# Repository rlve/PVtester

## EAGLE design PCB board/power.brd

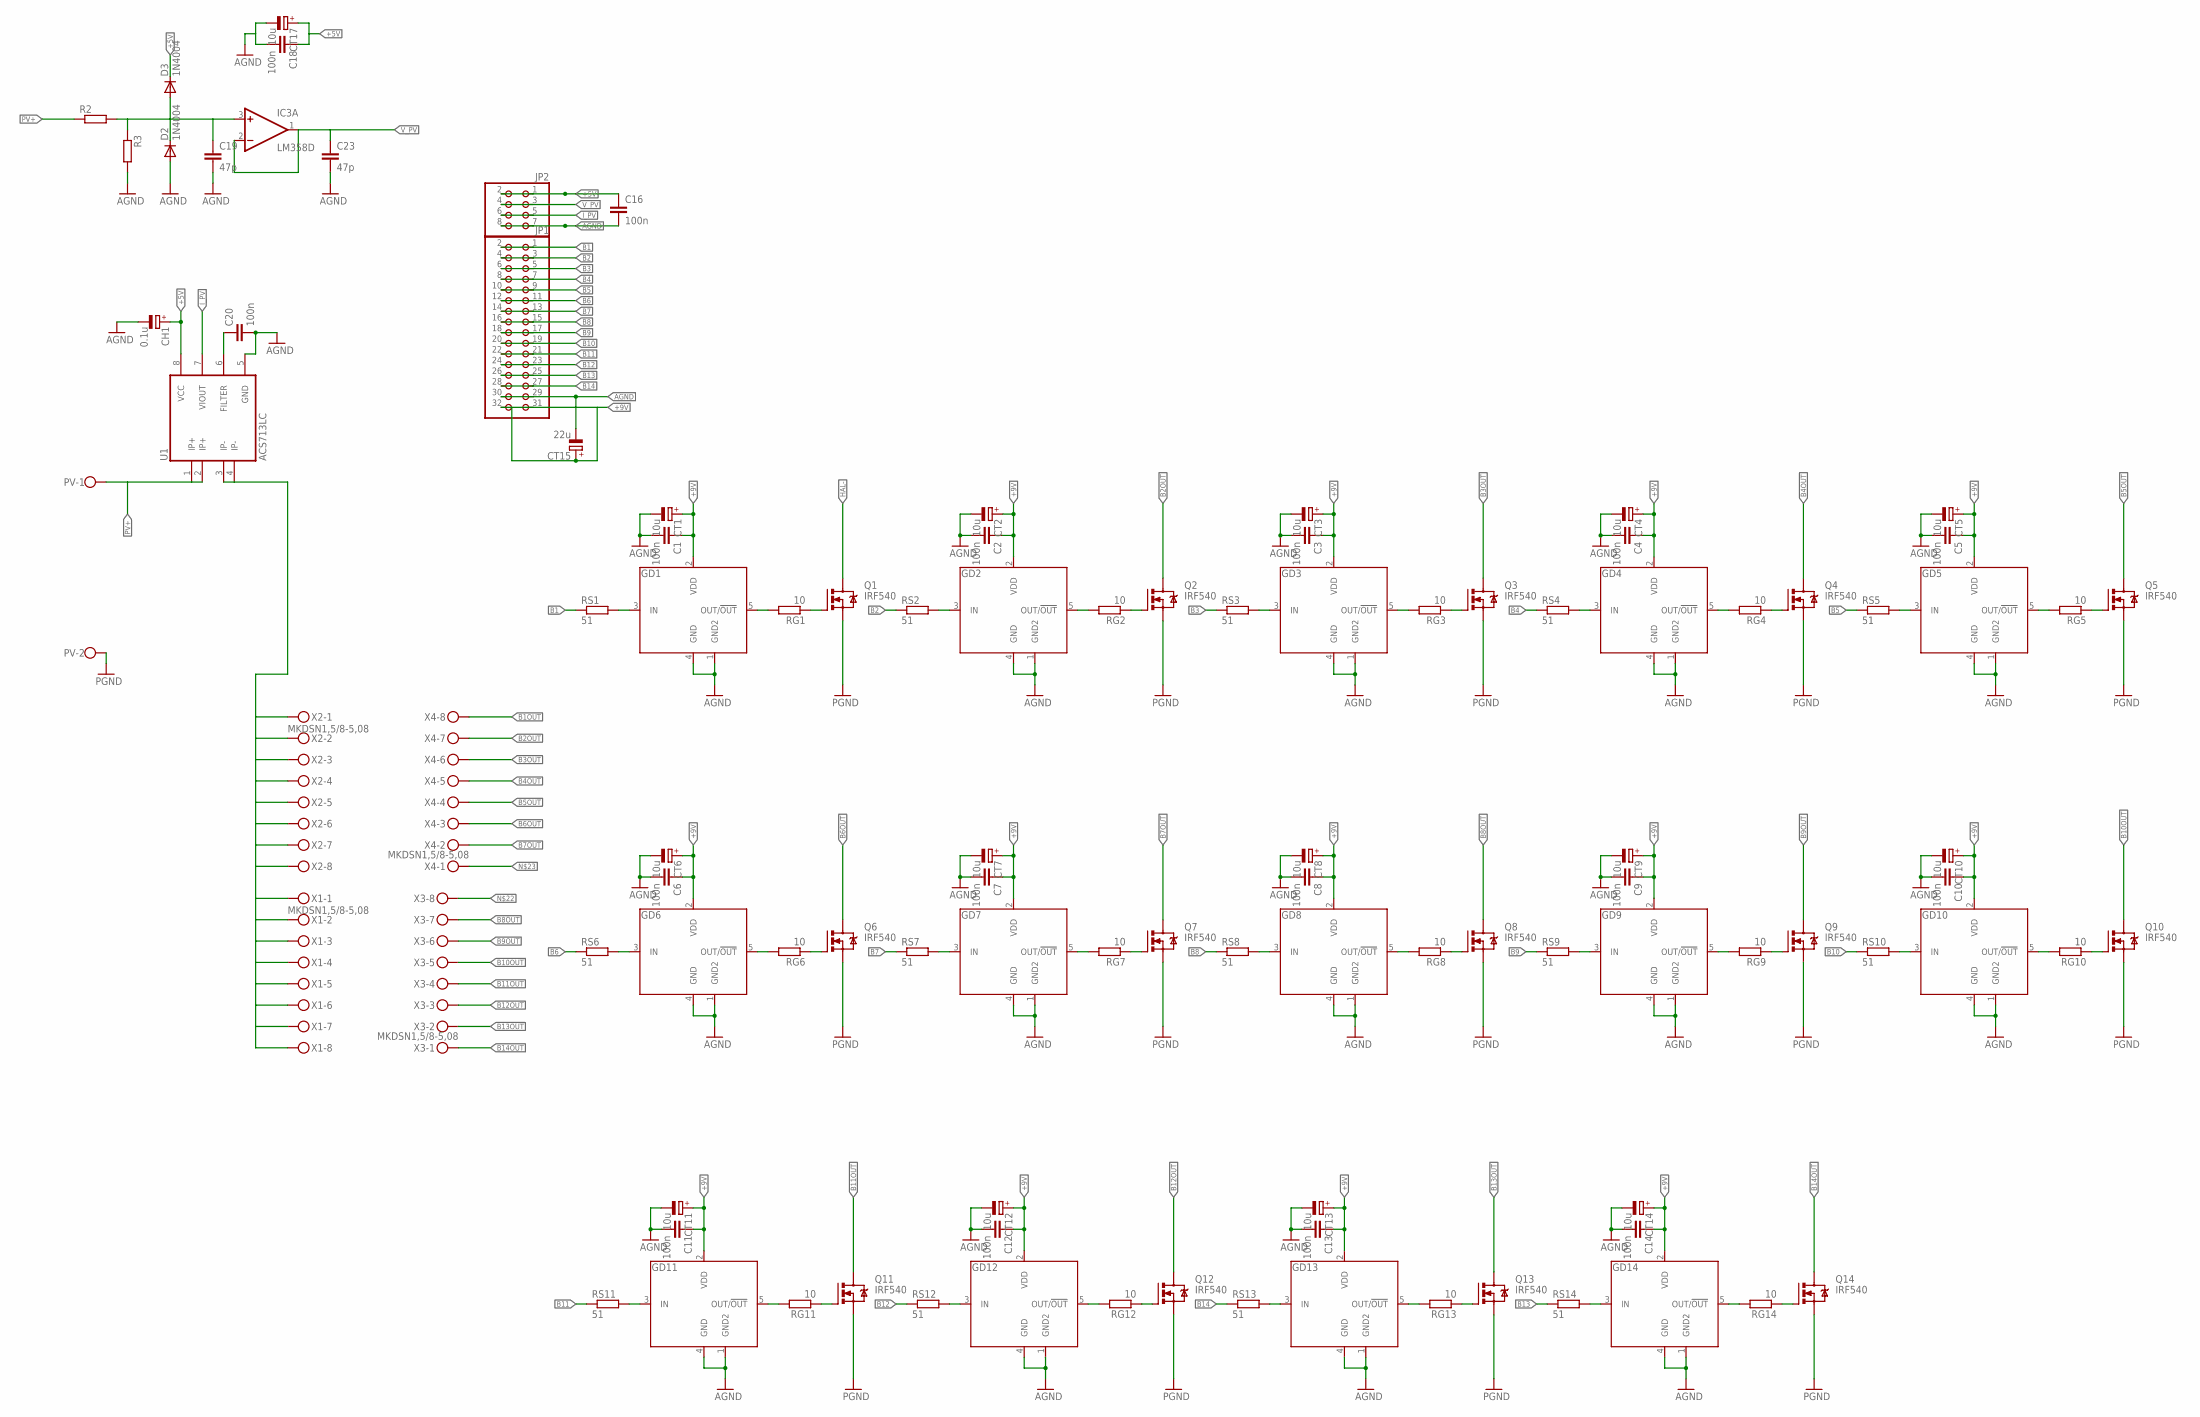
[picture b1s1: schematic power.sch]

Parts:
C1, C2, C3, C4, C5, C6, C7, C8, C9, C10, C11, C12, C13, C14, C16, C18, C20: 100n; C0603
C19, C23: 47p; C0603
CH1: 0.1u; B/3528-21W
CT1, CT2, CT3, CT4, CT5, CT6, CT7, CT8, CT9, CT10, CT11, CT12, CT13, CT14, CT17: 10u; B/3528-21W
CT15: 22u; B/3528-21W
D2, D3: 1N4004; DO214AC
GD1, GD2, GD3, GD4, GD5, GD6, GD7, GD8, GD9, GD10, GD11, GD12, GD13, GD14: MCP1415/16; SOT23-5L
IC3: LM358D; SO08
JP1: PINHD-2X16; 2X16
JP2: PINHD-2X4; 2X04
PV: W237-102
Q1, Q2, Q3, Q4, Q5, Q6, Q7, Q8, Q9, Q10, Q11, Q12, Q13, Q14: IRF540; TO220BV
R2, R3: R-EU_R1206; R1206
RG1, RG2, RG3, RG4, RG5, RG6, RG7, RG8, RG9, RG10, RG11, RG12, RG13, RG14: 10; R1206
RS1, RS2, RS3, RS4, RS5, RS6, RS7, RS8, RS9, RS10, RS11, RS12, RS13, RS14: 51; R1206
U1: ACS713LC; SO08
X1, X2, X3, X4: MKDSN1,5/8-5,08

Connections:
21: GD12.3 (IN), RS12.2
4524: GD10.3 (IN), RS10.2
24504: GD5.3 (IN), RS5.2
27872: GD13.3 (IN), RS13.2
85245: GD3.3 (IN), RS3.2
125204: GD7.3 (IN), RS7.2
152210: GD9.3 (IN), RS9.2
245242: GD11.3 (IN), RS11.2
254245: GD4.3 (IN), RS4.2
+5V: C16.1, C18.1, CH1.+, CT17.+, D3.C, IC3.8 (V+), JP2.1, JP2.2, U1.8 (VCC)
+9V: C1.1, C2.1, C3.1, C4.1, C5.1, C6.1, C7.1, C8.1, C9.1, C10.1, C11.1, C12.1, C13.1, C14.1, CT1.+, CT2.+, CT3.+, CT4.+, CT5.+, CT6.+, CT7.+, CT8.+, CT9.+, CT10.+, CT11.+, CT12.+, CT13.+, CT14.+, CT15.+, GD1.2 (VDD), GD2.2 (VDD), GD3.2 (VDD), GD4.2 (VDD), GD5.2 (VDD), GD6.2 (VDD), GD7.2 (VDD), GD8.2 (VDD), GD9.2 (VDD), GD10.2 (VDD), GD11.2 (VDD), GD12.2 (VDD), GD13.2 (VDD), GD14.2 (VDD), JP1.31, JP1.32
AGND: C1.2, C2.2, C3.2, C4.2, C5.2, C6.2, C7.2, C8.2, C9.2, C10.2, C11.2, C12.2, C13.2, C14.2, C16.2, C18.2, C19.2, C20.2, C23.2, CH1.-, CT1.-, CT2.-, CT3.-, CT4.-, CT5.-, CT6.-, CT7.-, CT8.-, CT9.-, CT10.-, CT11.-, CT12.-, CT13.-, CT14.-, CT15.-, CT17.-, D2.A, GD1.1 (GND2), GD1.4 (GND), GD2.1 (GND2), GD2.4 (GND), GD3.1 (GND2), GD3.4 (GND), GD4.1 (GND2), GD4.4 (GND), GD5.1 (GND2), GD5.4 (GND), GD6.1 (GND2), GD6.4 (GND), GD7.1 (GND2), GD7.4 (GND), GD8.1 (GND2), GD8.4 (GND), GD9.1 (GND2), GD9.4 (GND), GD10.1 (GND2), GD10.4 (GND), GD11.1 (GND2), GD11.4 (GND), GD12.1 (GND2), GD12.4 (GND), GD13.1 (GND2), GD13.4 (GND), GD14.1 (GND2), GD14.4 (GND), IC3.4 (V-), JP1.29, JP1.30, JP2.7, JP2.8, R3.2, U1.5 (GND)
B1: JP1.1, JP1.2, RS1.1
B1OUT: X4.8
B2: JP1.3, JP1.4, RS2.1
B2OUT: Q2.D, X4.7
B3: JP1.5, JP1.6, RS3.1
B3OUT: Q3.D, X4.6
B4: JP1.7, JP1.8, RS4.1
B4OUT: Q4.D, X4.5
B5: JP1.9, JP1.10, RS5.1
B5OUT: Q5.D, X4.4
B6: JP1.11, JP1.12, RS6.1
B6OUT: Q6.D, X4.3
B7: JP1.13, JP1.14, RS7.1
B7OUT: Q7.D, X4.2
B8: JP1.15, JP1.16, RS8.1
B8OUT: Q8.D, X3.7
B9: JP1.17, JP1.18, RS9.1
B9OUT: Q9.D, X3.6
B10: JP1.19, JP1.20, RS10.1
B10OUT: Q10.D, X3.5
B11: JP1.21, JP1.22, RS11.1
B11OUT: Q11.D, X3.4
B12: JP1.23, JP1.24, RS12.1
B12OUT: Q12.D, X3.3
B13: JP1.25, JP1.26, RS14.1
B13OUT: Q13.D, X3.2
B14: JP1.27, JP1.28, RS13.1
B14OUT: Q14.D, X3.1
DVFEWV: GD1.3 (IN), RS1.2
HAL-: Q1.D, U1.3 (IP-), U1.4 (IP-), X1.1, X1.2, X1.3, X1.4, X1.5, X1.6, X1.7, X1.8, X2.1, X2.2, X2.3, X2.4, X2.5, X2.6, X2.7, X2.8
I_PV: JP2.5, JP2.6, U1.7 (VIOUT)
unnamed: GD2.5 (OUT/!OUT), RG2.2
unnamed: Q1.G, RG1.1
unnamed: GD1.5 (OUT/!OUT), RG1.2
unnamed: Q2.G, RG2.1
unnamed: GD3.5 (OUT/!OUT), RG3.2
unnamed: Q3.G, RG3.1
unnamed: GD4.5 (OUT/!OUT), RG4.2
unnamed: Q4.G, RG4.1
unnamed: GD5.5 (OUT/!OUT), RG5.2
unnamed: Q5.G, RG5.1
unnamed: GD10.5 (OUT/!OUT), RG10.2
unnamed: Q10.G, RG10.1
unnamed: GD9.5 (OUT/!OUT), RG9.2
unnamed: Q9.G, RG9.1
unnamed: GD8.5 (OUT/!OUT), RG8.2
unnamed: Q8.G, RG8.1
unnamed: GD7.5 (OUT/!OUT), RG7.2
unnamed: Q7.G, RG7.1
unnamed: GD6.5 (OUT/!OUT), RG6.2
unnamed: Q6.G, RG6.1
unnamed: GD11.5 (OUT/!OUT), RG11.2
unnamed: Q11.G, RG11.1
unnamed: GD12.5 (OUT/!OUT), RG12.2
unnamed: Q12.G, RG12.1
unnamed: GD13.5 (OUT/!OUT), RG13.2
unnamed: Q13.G, RG13.1
unnamed: GD14.5 (OUT/!OUT), RG14.2
unnamed: Q14.G, RG14.1
unnamed: C19.1, D2.C, D3.A, IC3.3 (+IN), R2.2, R3.1
unnamed: C20.1, U1.6 (FILTER)
unnamed: GD2.3 (IN), RS2.2
unnamed: GD8.3 (IN), RS8.2
unnamed: GD6.3 (IN), RS6.2
unnamed: GD14.3 (IN), RS14.2
PGND: PV.2, Q1.S, Q2.S, Q3.S, Q4.S, Q5.S, Q6.S, Q7.S, Q8.S, Q9.S, Q10.S, Q11.S, Q12.S, Q13.S, Q14.S
PV+: PV.1, R2.1, U1.1 (IP+), U1.2 (IP+)
V_PV: C23.1, IC3.1 (OUT), IC3.2 (-IN), JP2.3, JP2.4

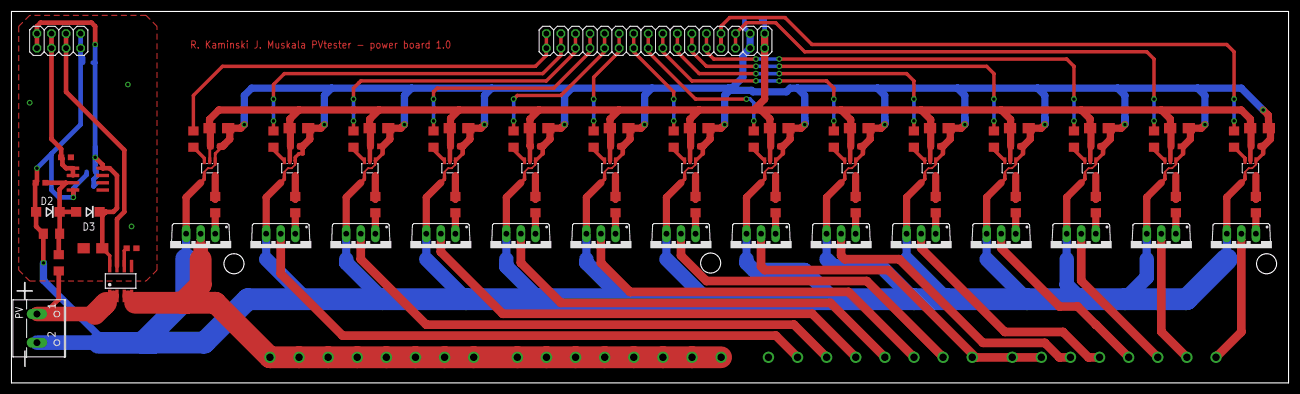
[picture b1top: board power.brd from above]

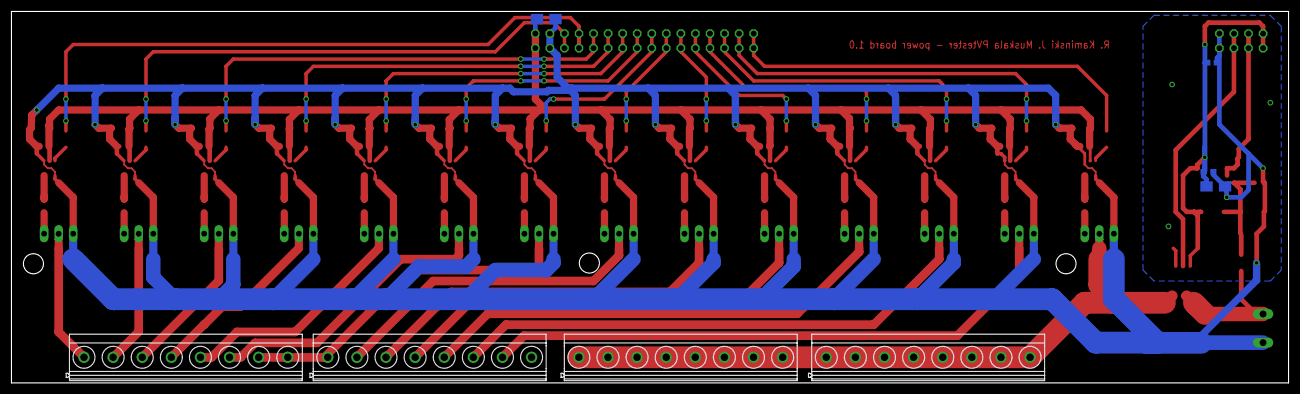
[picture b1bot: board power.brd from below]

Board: 2 copper layers, 222.9 x 64.8 mm, 105 parts (8 on the bottom side), 79 nets.

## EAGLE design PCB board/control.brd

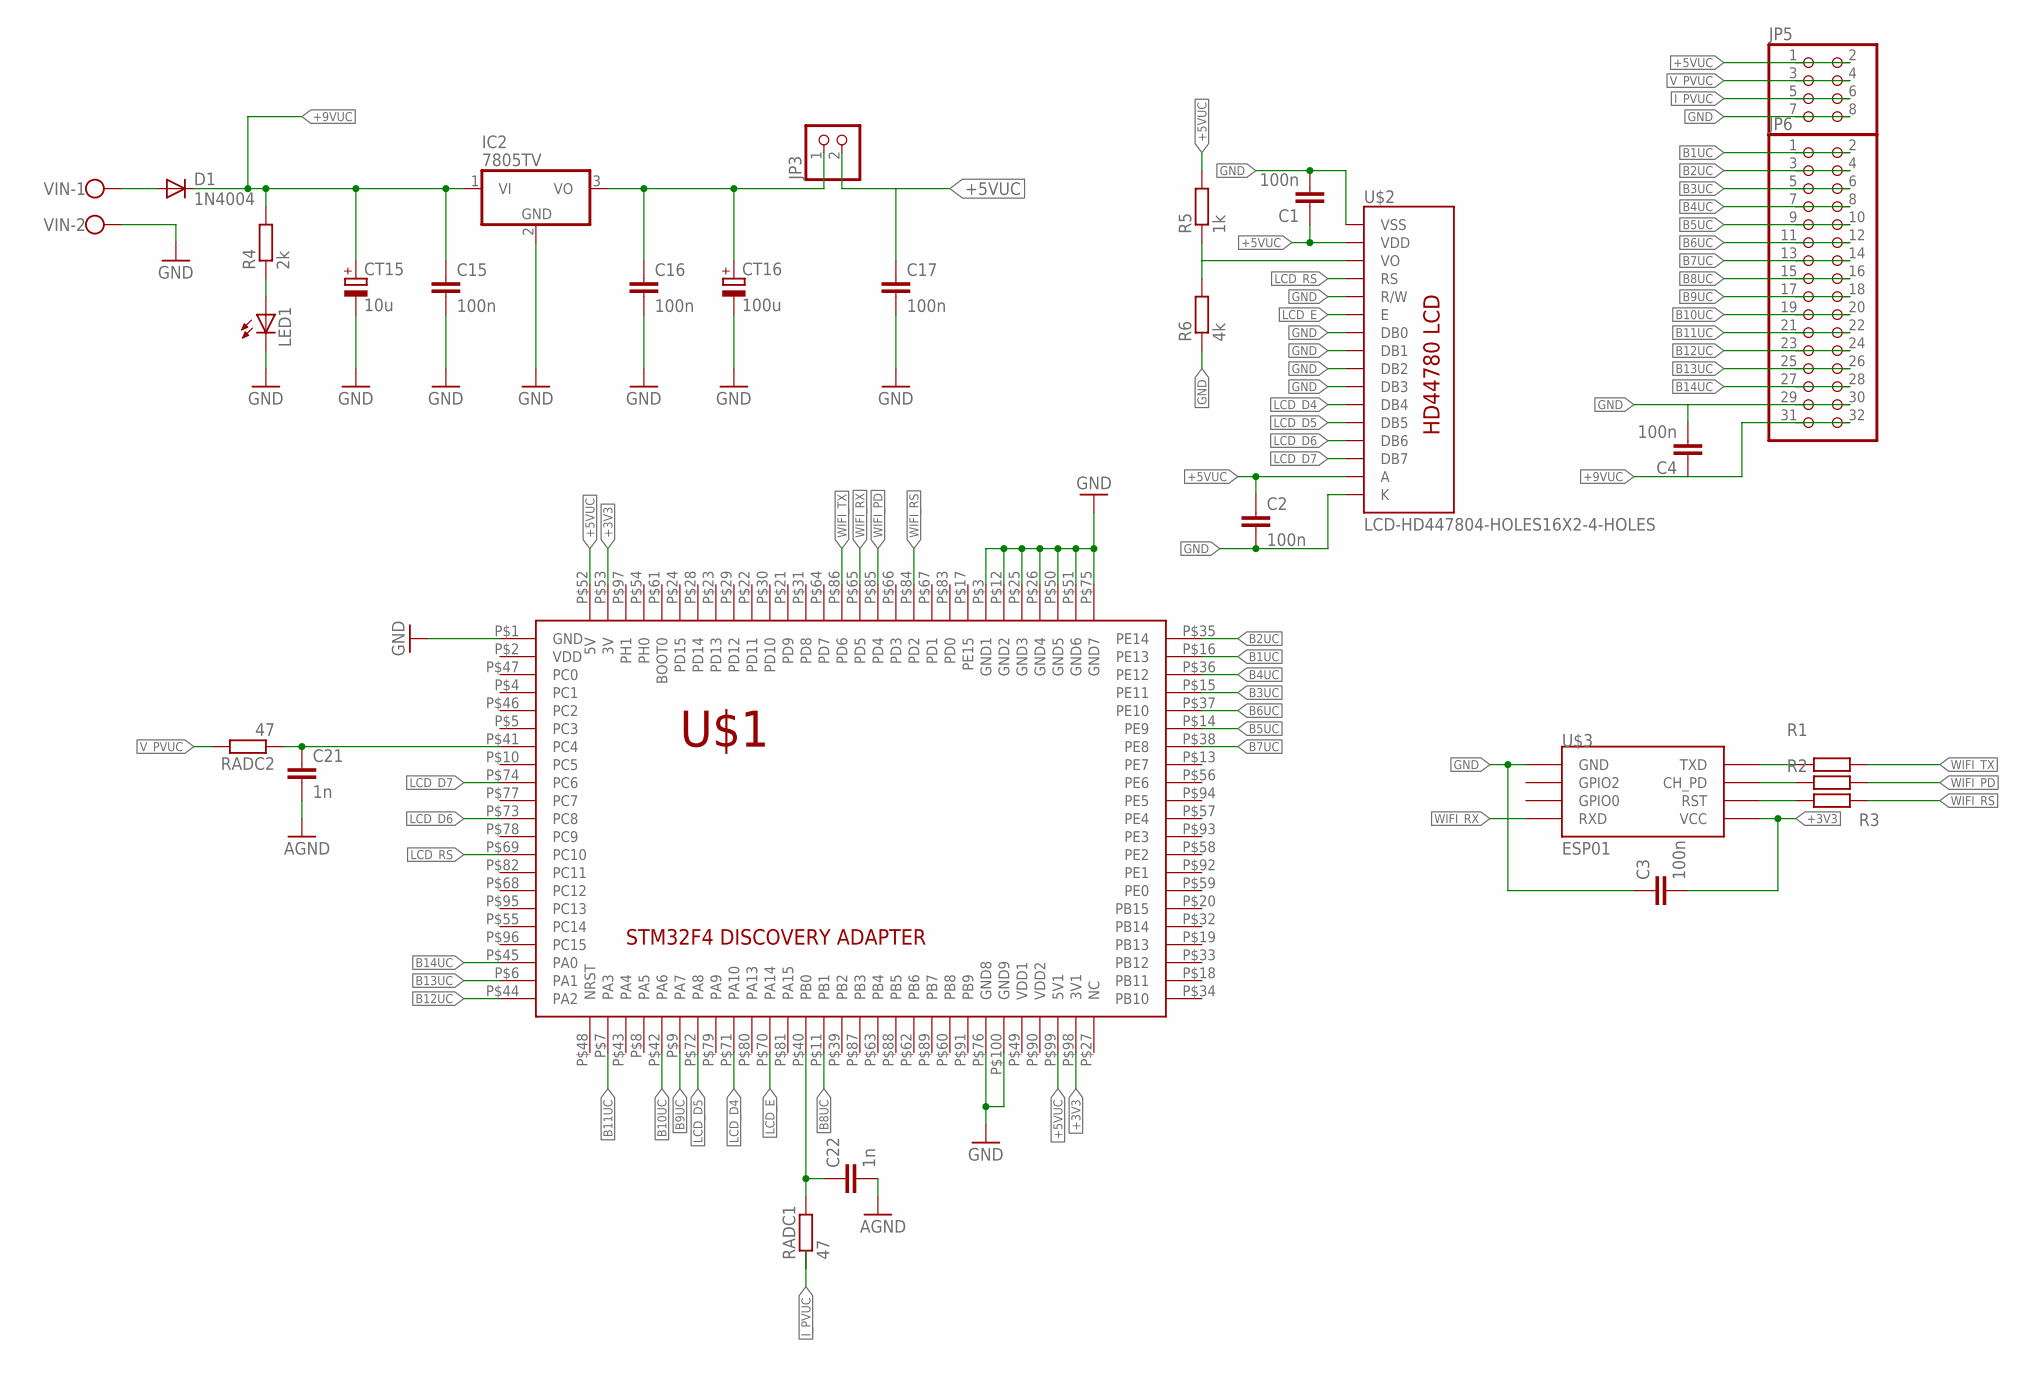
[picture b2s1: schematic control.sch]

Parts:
C1, C2, C3, C4, C15, C16, C17: 100n; C1206
C21, C22: 1n; C1206
CT15: 10u; B/3528-21W
CT16: 100u; D/7343-31R
D1: 1N4004; DO214AC
IC2: 7805TV; TO220V
JP3: PINHD-1X2; 1X02
JP5: PINHD-2X4/90; 2X04/90
JP6: PINHD-2X16/90; 2X16/90
LED1: LEDCHIPLED_0805; CHIPLED_0805
R1, R2, R3: R-EU_R0603; R0603
R4: 2k; M1206
R5: 1k; M1206
R6: 4k; M1206
RADC1, RADC2: 47; R1206
U$1: STM32F4ADAPTER; DISCOVERYPACK
U$2: LCD-HD447804-HOLES16X2-4-HOLES; LCD-16X2-4HOLES
U$3: ESP01
VIN: W237-102

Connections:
+3V3: C3.2, U$1.P$53 (3V), U$1.P$98 (3V1), U$3.VCC
+5VUC: C1.1, C2.1, C17.1, JP3.2, JP5.1, JP5.2, R5.2, U$1.P$52 (5V), U$1.P$99 (5V1), U$2.2 (VDD), U$2.15 (A)
+9VUC: C4.1, C15.1, CT15.+, D1.C, IC2.1 (VI), JP6.31, JP6.32, R4.2
B1UC: JP6.1, JP6.2, U$1.P$16 (PE13)
B2UC: JP6.3, JP6.4, U$1.P$35 (PE14)
B3UC: JP6.5, JP6.6, U$1.P$15 (PE11)
B4UC: JP6.7, JP6.8, U$1.P$36 (PE12)
B5UC: JP6.9, JP6.10, U$1.P$14 (PE9)
B6UC: JP6.11, JP6.12, U$1.P$37 (PE10)
B7UC: JP6.13, JP6.14, U$1.P$38 (PE8)
B8UC: JP6.15, JP6.16, U$1.P$11 (PB1)
B9UC: JP6.17, JP6.18, U$1.P$9 (PA7)
B10UC: JP6.19, JP6.20, U$1.P$42 (PA6)
B11UC: JP6.21, JP6.22, U$1.P$7 (PA3)
B12UC: JP6.23, JP6.24, U$1.P$44 (PA2)
B13UC: JP6.25, JP6.26, U$1.P$6 (PA1)
B14UC: JP6.27, JP6.28, U$1.P$45 (PA0)
GND: C1.2, C2.2, C3.1, C4.2, C15.2, C16.2, C17.2, C21.2, C22.2, CT15.-, CT16.-, IC2.2 (GND), JP5.7, JP5.8, JP6.29, JP6.30, LED1.C, R6.1, U$1.P$1 (GND), U$1.P$3 (GND1), U$1.P$12 (GND2), U$1.P$25 (GND3), U$1.P$26 (GND4), U$1.P$50 (GND5), U$1.P$51 (GND6), U$1.P$75 (GND7), U$1.P$76 (GND8), U$1.P$100 (GND9), U$2.1 (VSS), U$2.5 (R/W), U$2.7 (DB0), U$2.8 (DB1), U$2.9 (DB2), U$2.10 (DB3), U$2.16 (K), U$3.GND, VIN.2
I_PVUC: JP5.5, JP5.6, RADC1.1
LCD_D4: U$1.P$71 (PA10), U$2.11 (DB4)
LCD_D5: U$1.P$72 (PA8), U$2.12 (DB5)
LCD_D6: U$1.P$73 (PC8), U$2.13 (DB6)
LCD_D7: U$1.P$74 (PC6), U$2.14 (DB7)
LCD_E: U$1.P$70 (PA14), U$2.6 (E)
LCD_RS: U$1.P$69 (PC10), U$2.4 (RS)
unnamed: R1.1, U$3.TX (TXD)
unnamed: R2.1, U$3.CH_PD
unnamed: R3.1, U$3.RST
unnamed: C22.1, RADC1.2, U$1.P$40 (PB0)
unnamed: LED1.A, R4.1
unnamed: C16.1, CT16.+, IC2.3 (VO), JP3.1
unnamed: R5.1, R6.2, U$2.3 (VO)
unnamed: D1.A, VIN.1
unnamed: C21.1, RADC2.1, U$1.P$41 (PC4)
V_PVUC: JP5.3, JP5.4, RADC2.2
WIFI_PD: R2.2, U$1.P$85 (PD4)
WIFI_RS: R3.2, U$1.P$84 (PD2)
WIFI_RX: U$1.P$65 (PD5), U$3.RX (RXD)
WIFI_TX: R1.2, U$1.P$86 (PD6)

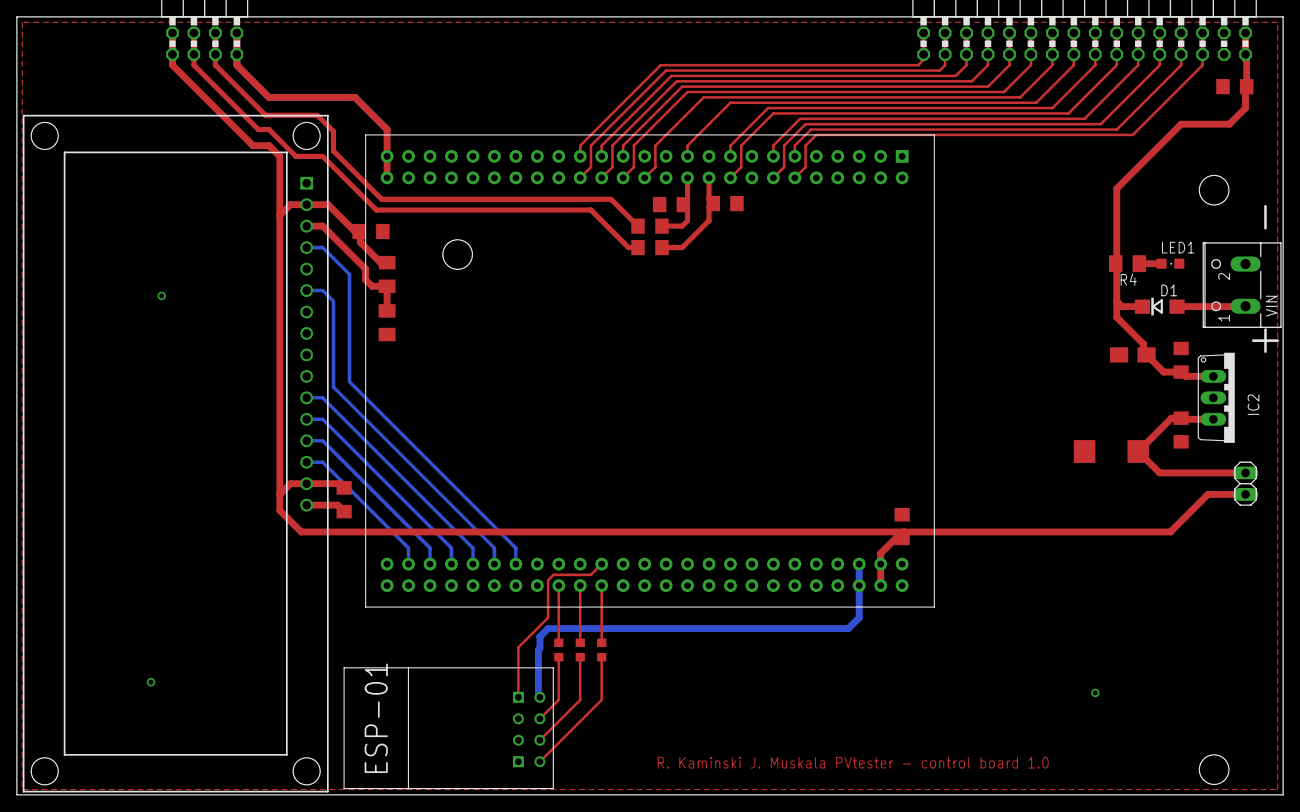
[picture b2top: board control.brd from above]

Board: 2 copper layers, 149.9 x 92.1 mm, 29 parts (1 on the bottom side), 39 nets.

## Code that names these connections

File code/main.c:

#include "stm32f4xx.h"
#include "bb.h"
#include "gpio.h"
#include "pvtest_gpio_config.h"
#include "pvtest_uc_config.h"
#include "pvtest_tim_config.h"
#include "pvtest_adcdma_config.h"

volatile uint8_t timer_cycles=0;							//main timer cycles counter
extern uint16_t *wyniki;
	int tim3=0;
	int tim2=0;
	int licznik=0;

int main(void){
	Initialization_uC();
	GPIO_configuration();
	Timer_configuration();
	ADCDMA_configuration();

	LED3_Toggle;
//	timer_cycles=0;										//clear counter
//	TIM2->CR1|=TIM_CR1_CEN; 							//turn on timer

//	LED1_Toggle;
//
//	RCC->APB1LPENR |= RCC_APB1LPENR_TIM2LPEN; 				//enable clock in sleep mode
//	RCC->APB1LPENR |= RCC_APB1LPENR_TIM3LPEN; 				//enable clock in sleep mode
//	RCC->AHB1LPENR |= RCC_AHB1LPENR_DMA2LPEN; 		//enable clock in sleep mode
//	RCC->APB2LPENR |= RCC_APB2LPENR_ADC1LPEN;		//enable clock in sleep mode
//	RCC->APB2LPENR |= RCC_APB2LPENR_TIM1LPEN;

	DBGMCU->CR |= DBGMCU_CR_DBG_SLEEP;
	SCB->SCR |= SCB_SCR_SLEEPONEXIT_Msk; 					//enter sleep on return from an interrupt service routine
	__WFI();												//sleeping mode, wait for interrupt
}
void EXTI0_IRQHandler(void){
	if(EXTI->PR&EXTI_PR_PR0){								//check interrupt flag
		EXTI->PR=EXTI_PR_PR0;								//clear flag

//		LED3_On;
//		LED4_On;
		timer_cycles=0;										//clear counter
		TIM2->CR1|=TIM_CR1_CEN; 							//turn on timer
		RCC->APB1LPENR |= RCC_APB1LPENR_TIM2LPEN; 				//enable clock in sleep mode
		RCC->APB1LPENR |= RCC_APB1LPENR_TIM3LPEN; 				//enable clock in sleep mode
		RCC->AHB1LPENR |= RCC_AHB1LPENR_DMA2LPEN; 		//enable clock in sleep mode
		RCC->APB2LPENR |= RCC_APB2LPENR_ADC1LPEN;		//enable clock in sleep mode
		RCC->APB2LPENR |= RCC_APB2LPENR_TIM1LPEN;
	}
}

 void TIM2_IRQHandler(void){
	 if(TIM2->SR & TIM_SR_UIF){								//checking interrupt flag
	 		TIM2->SR &= ~TIM_SR_UIF;								//clear flag
//	 		++tim2;
	 		LED1_Toggle;
	 		LED3_Toggle;
	 		MOSFET_control(timer_cycles);

//	 		/* pwm test */
//	 		if (++licznik<20)
//	 		{
//	 		TIM1->CCR4 = licznik;}
//	 		else if (licznik>=20){licznik=0;}

		if(++timer_cycles>=87){								//increase counter, if reaches threshold, disable timer
			TIM2->CR1^=TIM_CR1_CEN;
//			ADC1->SR &= ~(ADC_SR_EOC);
			RCC->APB1LPENR &= ~(RCC_APB1LPENR_TIM2LPEN); 		//disable clock in sleep mode
			RCC->APB1LPENR &= ~(RCC_APB1LPENR_TIM3LPEN); 		//disable clock in sleep mode
			RCC->AHB1LPENR &= ~(RCC_AHB1LPENR_DMA2LPEN); 		//disable clock in sleep mode
			RCC->APB2LPENR &= ~(RCC_APB2LPENR_ADC1LPEN);		//disable clock in sleep mode
			RCC->APB2LPENR &= ~(RCC_APB2LPENR_TIM1LPEN);

//			LED3_Off;
//			LED4_Off;
		}
	}
 }

//void TIM3_IRQHandler(void){
//	if(TIM3->SR & TIM_SR_UIF){								//checking interrupt flag
//		TIM3->SR &= ~TIM_SR_UIF;							//clear flag
//		LED3_Toggle;
//		++tim3;
//	}
//}
//
//void ADC_IRQHandler(void){
//
//		LED4_Toggle;
////		printf(wyniki[0], wyniki[1]);
//}

/*
void SysTick_Handler(void){
		BB(GPIOD->ODR, PD13) ^= 1;
	}
*/

void test_run(uint8_t counter){

	//	 BB(GPIOA->ODR,PA1)=1;		//R1
	//	 BB(GPIOA->ODR,PA1)=0;		//R1
	//
	//	 BB(GPIOA->ODR,PA0)=1;		//R2
	//	 BB(GPIOA->ODR,PA0)=0;		//R2
	//
	//	 BB(GPIOA->ODR,PA2)=1;		//R3
	//	 BB(GPIOA->ODR,PA2)=0;		//R3
	//
	//	 BB(GPIOA->ODR,PA3)=1;		//R4
	//	 BB(GPIOA->ODR,PA3)=0;		//R4
	//
	//	 BB(GPIOA->ODR,PA6)=1;		//R5
	//	 BB(GPIOA->ODR,PA6)=0;		//R5
	//
	//	 BB(GPIOA->ODR,PA7)=1;		//R6
	//	 BB(GPIOA->ODR,PA7)=0;		//R6
	//
	//	 BB(GPIOB->ODR,PB1)=1;		//R7
	//	 BB(GPIOB->ODR,PB1)=0;		//R7
	//
	//	 BB(GPIOE->ODR,PE8)=1;		//R8
	//	 BB(GPIOE->ODR,PE8)=0;		//R8
	//
	//	 BB(GPIOE->ODR,PE10)=1;		//R9
	//	 BB(GPIOE->ODR,PE10)=0;		//R9
	//
	//	 BB(GPIOE->ODR,PE9)=1;		//R10
	//	 BB(GPIOE->ODR,PE9)=0;		//R10
	//
	//	 BB(GPIOE->ODR,PE12)=1;		//R11
	//	 BB(GPIOE->ODR,PE12)=0;		//R11
	//
	//	 BB(GPIOE->ODR,PE11)=1;		//R12
	//	 BB(GPIOE->ODR,PE11)=0;		//R12
	//
	//	 BB(GPIOE->ODR,PE14)=1;		//R13
	//	 BB(GPIOE->ODR,PE14)=0;		//R13
	//
	//	 BB(GPIOE->ODR,PE13)=1;		//R14
	//	 BB(GPIOE->ODR,PE13)=0;		//R14

}

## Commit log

2017-05-30 :boom::camel: Added .gitattributes & .gitignore files
2017-05-30 Add: uC codes and project of pcb boards
    Just to save original files. Perhaps someday I'll return here...

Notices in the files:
parts and their libraries:
allegro-micro: Copyright (C) 2008, Bob Starr
